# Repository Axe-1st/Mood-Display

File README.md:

# Mood-Display
## A Round Pin badge display! Powered by an Integrated ESP32-S3-WROOM-1 and a 1.28 in round display MoodBadge clips easily to your ID lanyard, keychain, belt, Bag, and so many more. You can easily express your mood or any animations you want to play on the display!

> Hiya! This project is still in its designing stage! When i build it, I will make a step by step video how to assemble 

> PDF is available in Zine folder!

### I made this project because i was inspired by those mini circular displays that you can bring anywhere! 
### This exsist since i wanted a badge that i can interact with.
### This project is pretty easy to do, All you need to do is follow the tutorial (Scoll down)

### Some kind of important notes!
- This is powered by USB C <b>ONLY</b>
- yes that means you have to always have a powerbank around with u to power it!
- reason for this: It would increase project cost and its complexity. 

## Schematic

> for a much better image check the pdf in extras!

## PCB

## PCB Render
- back

- Front

## Cad
- Onshape link:https://cad.onshape.com/documents/fe18899c0fc823d496ae247b/w/1ef647bd25a6a14e89f050fb/e/3a17c80e85047fb88fb13b3e?renderMode=0&uiState=6a0dad73ebc90dae0eac1fbd

> I love Onshape Man

## How to Build it 
- 1st step: Get the Requied materials in BOM.CSV and get the Gerber file in the folder production.
- 2nd Step: Pay JLC PCB to Fabricate the PCB and Use the links in the BOM.CSV to order parts
> You should def order a stencil! But for this tutorial i will be doing it manualy

- 3rd Step: Get your solder paste then manualy little solder to each pad that needs a connection. Also have a tissue nearby!
> Remember Patience is better than Crashing Out!

- 4th step: Start placing the compoments then when you are ready, use a hot plate to reflow all of the connections!
> For this part you would be Placing compoments at the back of the pcb so that means the front side of the pcb is facing flat on the hotplate
> When reflowing feel free to gently adjust the possiton of the compoments!

- 5th step: Now you have the backside of the pcb done! After letting the PCB rest now flip it to the other side, you should see some pads there. You are going to use a normal soldering iron to solder the buttons and other DIP compoments like the power Headers!

- 6th Step: Congradulations! You are done with the PCB!! Now kindly please test it by powering it on with a type C cable (please make sure it gets enough power to boot). Flash the test firmware i have provided it should light up the leds!

- if you like the bare PCB you can now stop here and use any of the mounting holes to attach the Mood-Display with anything!

- After this it would be Optional to do the case!

- 7th Step: Print all of the Case Parts then start assembling it by starting with the bottom. With the Bottom place the pcb on top and it line up with the mounting holes! When it is fully alligned screw the holes! Now get your assembles Bottom Case and carefully insert it up to the "middle case part" then super glue it! Now place and glue the Top Cover!
> i have used the terms "bottom case" "Middle Part" "Top Cover" why? because i have provided three parts in the CAD. 

- Final Step: There is no final step Lmao. Enjoy your own Mood display!

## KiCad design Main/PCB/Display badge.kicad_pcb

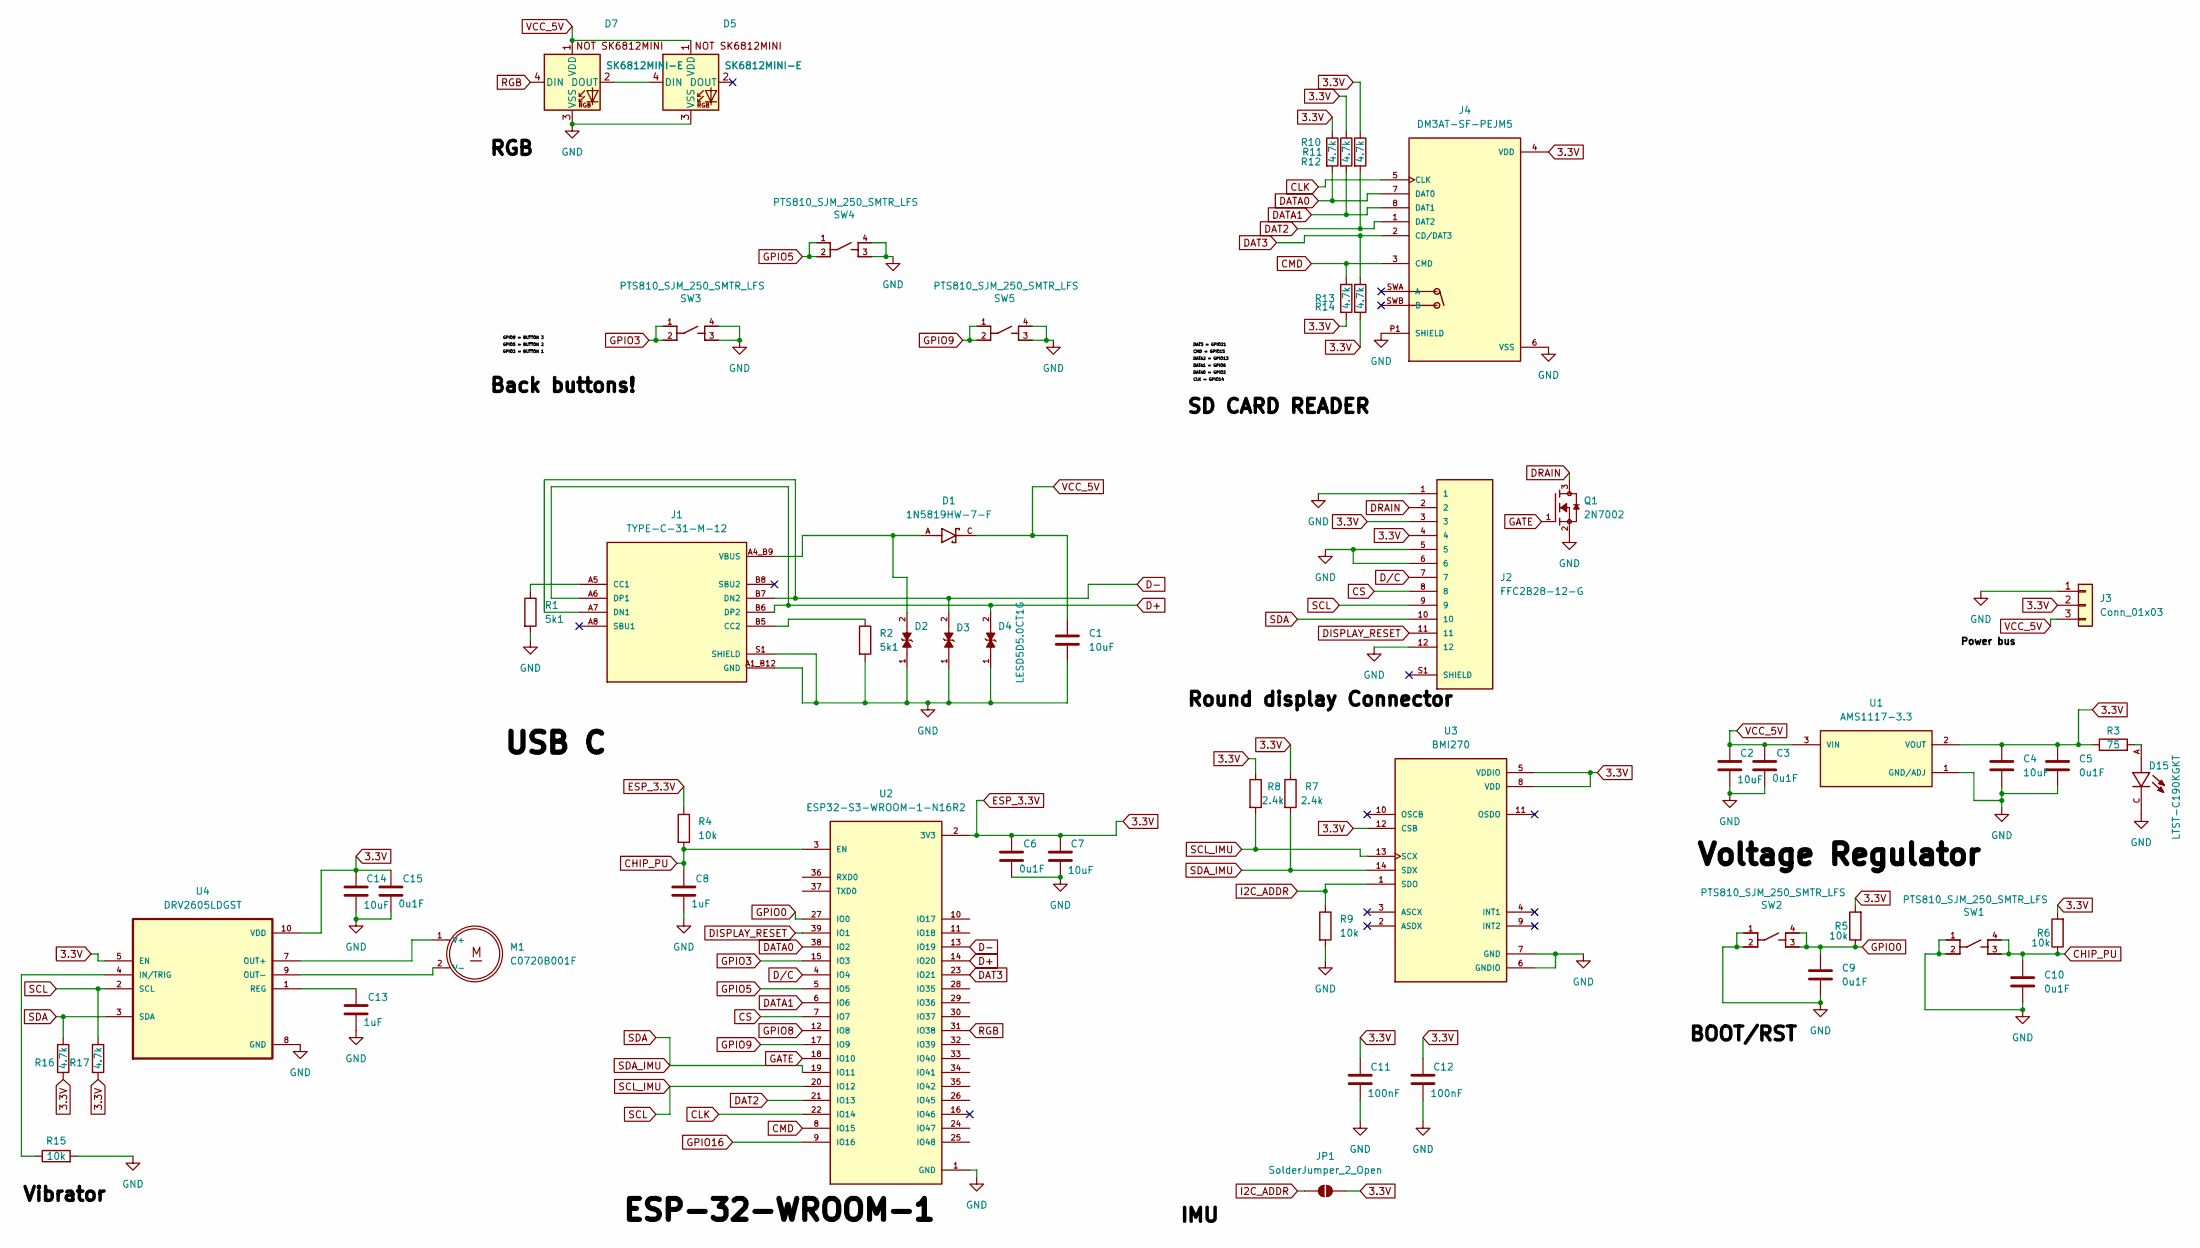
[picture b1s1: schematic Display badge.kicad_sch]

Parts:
C1, C2, C4, C7, C14: 10uF; C_0805_2012Metric_Pad1.18x1.45mm_HandSolder
C3, C5, C6, C9, C10, C15: 0u1F; C_0805_2012Metric_Pad1.18x1.45mm_HandSolder
C8, C13: 1uF; C_0805_2012Metric_Pad1.18x1.45mm_HandSolder
C11, C12: 100nF; C_0805_2012Metric_Pad1.18x1.45mm_HandSolder
D1: 1N5819HW-7-F; SOD3715X145N; PARTREV 18-2
D2, D3, D4: LESD5D5.0CT1G; TVS_LESD5D5.0CT1G; PARTREV O
D5, D7: SK6812MINI-E; SK6812MINI-E_fixed
D15: LTST-C190KGKT; LEDC1608X35N
J1: TYPE-C-31-M-12; HRO_TYPE-C-31-M-12; PARTREV 2020.12.08
J2: FFC2B28-12-G; GCT_FFC2B28-12-G; PARTREV A
J3: Conn_01x03; PinSocket_1x03_P2.00mm_Vertical
J4: DM3AT-SF-PEJM5; HRS_DM3AT-SF-PEJM5; PARTREV 20200913
JP1: SolderJumper_2_Open; SolderJumper-2_P1.3mm_Open_RoundedPad1.0x1.5mm
M1: C0720B001F; XDCR_C0720B001F
Q1: 2N7002; TRANS_2N7002; PARTREV 2023-01-11
R1, R2: 5k1; R_0805_2012Metric_Pad1.20x1.40mm_HandSolder
R3: 75; R_0805_2012Metric_Pad1.20x1.40mm_HandSolder
R4, R5, R6, R9, R15: 10k; R_0603_1608Metric_Pad0.98x0.95mm_HandSolder
R7, R8: 2.4k; RES_ERA2AEB242X
R10, R11, R12, R13, R14, R16, R17: 4.7k; R_0603_1608Metric_Pad0.98x0.95mm_HandSolder
SW1, SW2, SW3, SW4, SW5: PTS810_SJM_250_SMTR_LFS; SW_PTS810_SJM_250_SMTR_LFS
U1: AMS1117-3.3; SOT229P700X180-4N; PARTREV N/A
U2: ESP32-S3-WROOM-1-N16R2; XCVR_ESP32-S3-WROOM-1-N16R2; PARTREV v1.0
U3: BMI270; XDCR_BMI270
U4: DRV2605LDGST; SOP50P490X110-10N

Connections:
3.3V: C4.1, C5.1, C6.1, C7.1, C11.1, C12.1, C14.1, C15.1, J2.3, J2.4, J3.2, J4.4 (VDD), JP1.2 (B), R3.1, R4.1, R5.2, R6.2, R7.1, R8.1, R10.1, R11.1, R12.1, R13.2, R14.2, R16.2, R17.2, U1.2 (VOUT), U2.2 (3V3), U3.5 (VDDIO), U3.8 (VDD), U3.12 (CSB), U4.5 (EN), U4.10 (VDD)
CHIP_PU: C8.1, C10.1, R4.2, R6.1, SW1.3, SW1.4, U2.3 (EN)
CLK: J4.5 (CLK), U2.22 (IO14)
CMD: J4.3 (CMD), R13.1, U2.8 (IO15)
CS: J2.8, U2.7 (IO7)
D+: D4.2, J1.A6 (DP1), J1.B6 (DP2), U2.14 (IO20)
D-: D3.2, J1.A7 (DN1), J1.B7 (DN2), U2.13 (IO19)
DAT2: J4.1 (DAT2), R12.2, U2.21 (IO13)
DAT3: J4.2 (CD/DAT3), R14.1, U2.23 (IO21)
DATA0: J4.7 (DAT0), R10.2, U2.38 (IO2)
DATA1: J4.8 (DAT1), R11.2, U2.6 (IO6)
DISPLAY_RESET: J2.11, U2.39 (IO1)
DRAIN: J2.2, Q1.3
D/C: J2.7, U2.4 (IO4)
GATE: Q1.1, U2.18 (IO10)
GND: C1.2, C2.2, C3.2, C4.2, C5.2, C6.2, C7.2, C8.2, C9.2, C10.2, C11.2, C12.2, C13.2, C14.2, C15.2, D2.1, D3.1, D4.1, D5.3 (VSS), D7.3 (VSS), D15.C, J1.A1_B12 (GND), J1.B1_A12 (GND), J1.S1 (SHIELD), J1.S2 (SHIELD), J1.S3 (SHIELD), J1.S4 (SHIELD), J2.1, J2.5, J2.6, J2.12, J3.1, J4.6 (VSS), J4.P1 (SHIELD), J4.P2 (SHIELD), J4.P3 (SHIELD), J4.P4 (SHIELD), Q1.2, R1.2, R2.2, R9.2, R15.2, SW1.1, SW1.2, SW2.1, SW2.2, SW3.3, SW3.4, SW4.3, SW4.4, SW5.3, SW5.4, U1.1 (GND/ADJ), U2.1 (GND), U2.40 (GND), U2.41_1 (GND), U2.41_2 (GND), U2.41_3 (GND), U2.41_4 (GND), U2.41_5 (GND), U2.41_6 (GND), U2.41_7 (GND), U2.41_8 (GND), U2.41_9 (GND), U3.6 (GNDIO), U3.7 (GND), U4.8 (GND)
GPIO0: C9.1, R5.1, SW2.3, SW2.4, U2.27 (IO0)
GPIO3: SW3.1, SW3.2, U2.15 (IO3)
GPIO5: SW4.1, SW4.2, U2.5 (IO5)
GPIO8: U2.12 (IO8)
GPIO9: SW5.1, SW5.2, U2.17 (IO9)
GPIO16: U2.9 (IO16)
I2C_ADDR: JP1.1 (A), R9.1, U3.1 (SDO)
unnamed: D5.4 (DIN), D7.2 (DOUT)
unnamed: D15.A, R3.2
unnamed: J1.A5 (CC1), R1.1
unnamed: J1.B5 (CC2), R2.1
unnamed: M1.1 (V+), U4.7 (OUT+)
unnamed: M1.2 (V-), U4.9 (OUT-)
unnamed: R15.1, U4.4 (IN/TRIG)
unnamed: C13.1, U4.1 (REG)
RGB: D7.4 (DIN), U2.31 (IO38)
SCL: J2.9, R8.2, R17.1, U2.20 (IO12), U3.13 (SCX), U4.2 (SCL)
SDA: J2.10, R7.2, R16.1, U2.19 (IO11), U3.14 (SDX), U4.3 (SDA)
VBUS: D1.A, D2.2, J1.A4_B9 (VBUS), J1.B4_A9 (VBUS)
VCC_5V: C1.1, C2.1, C3.1, D1.C, D5.1 (VDD), D7.1 (VDD), J3.3, U1.3 (VIN)

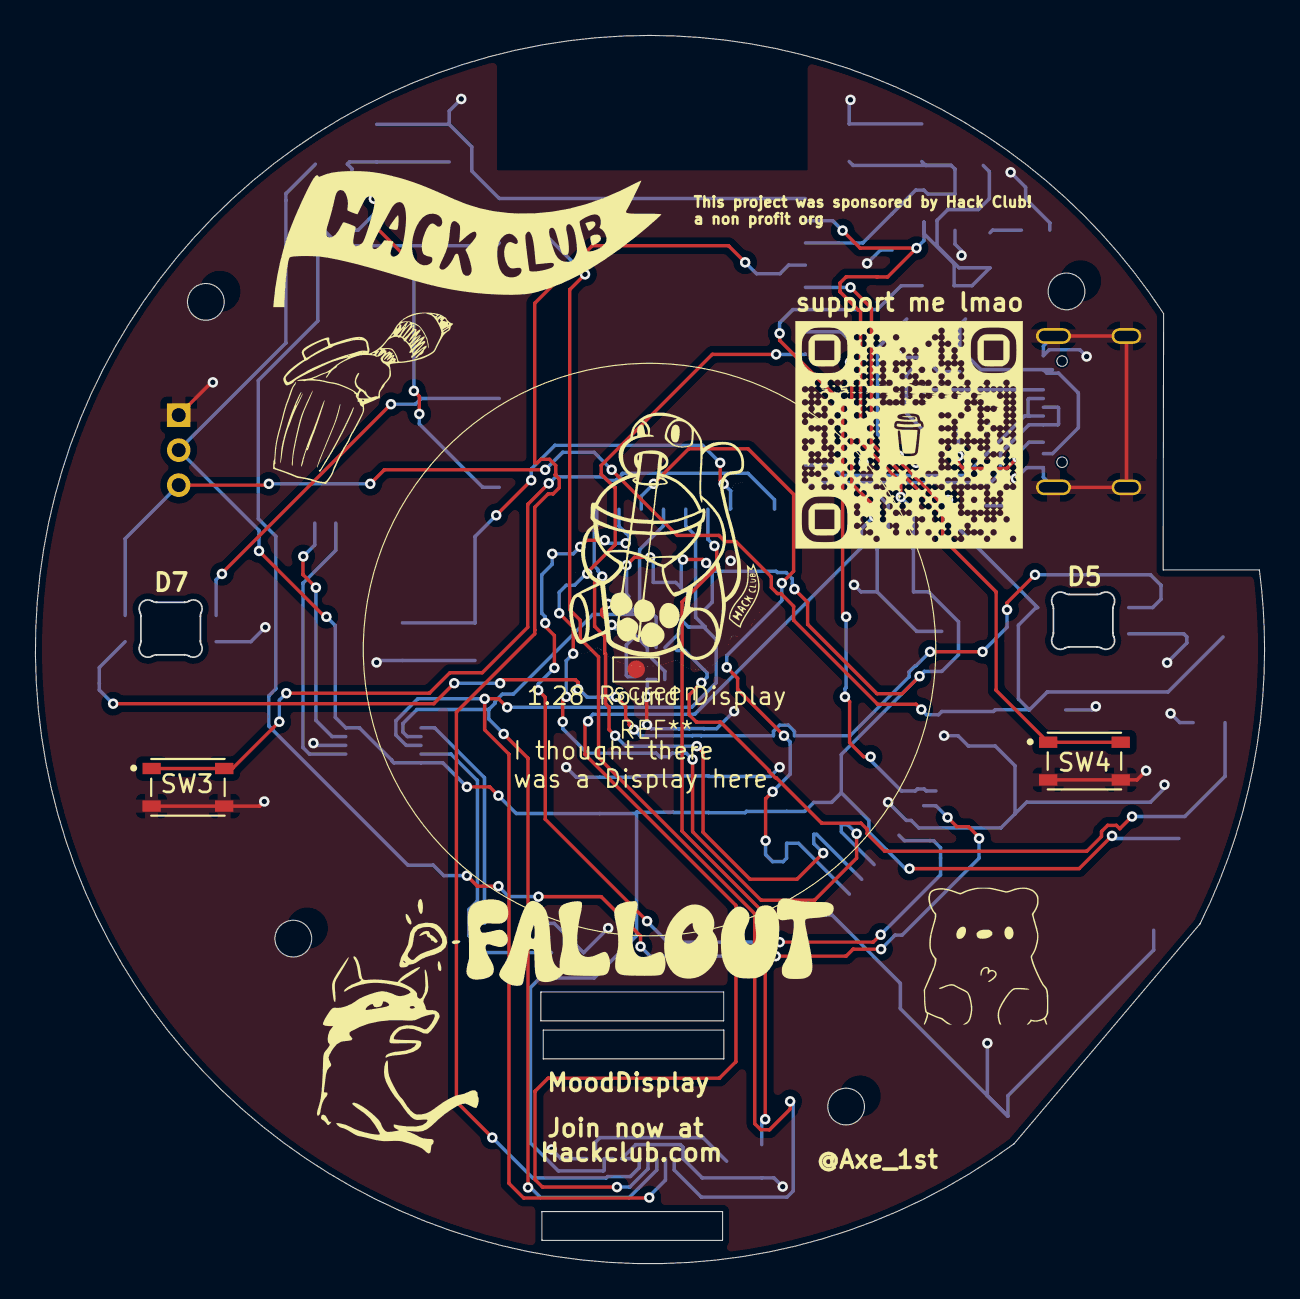
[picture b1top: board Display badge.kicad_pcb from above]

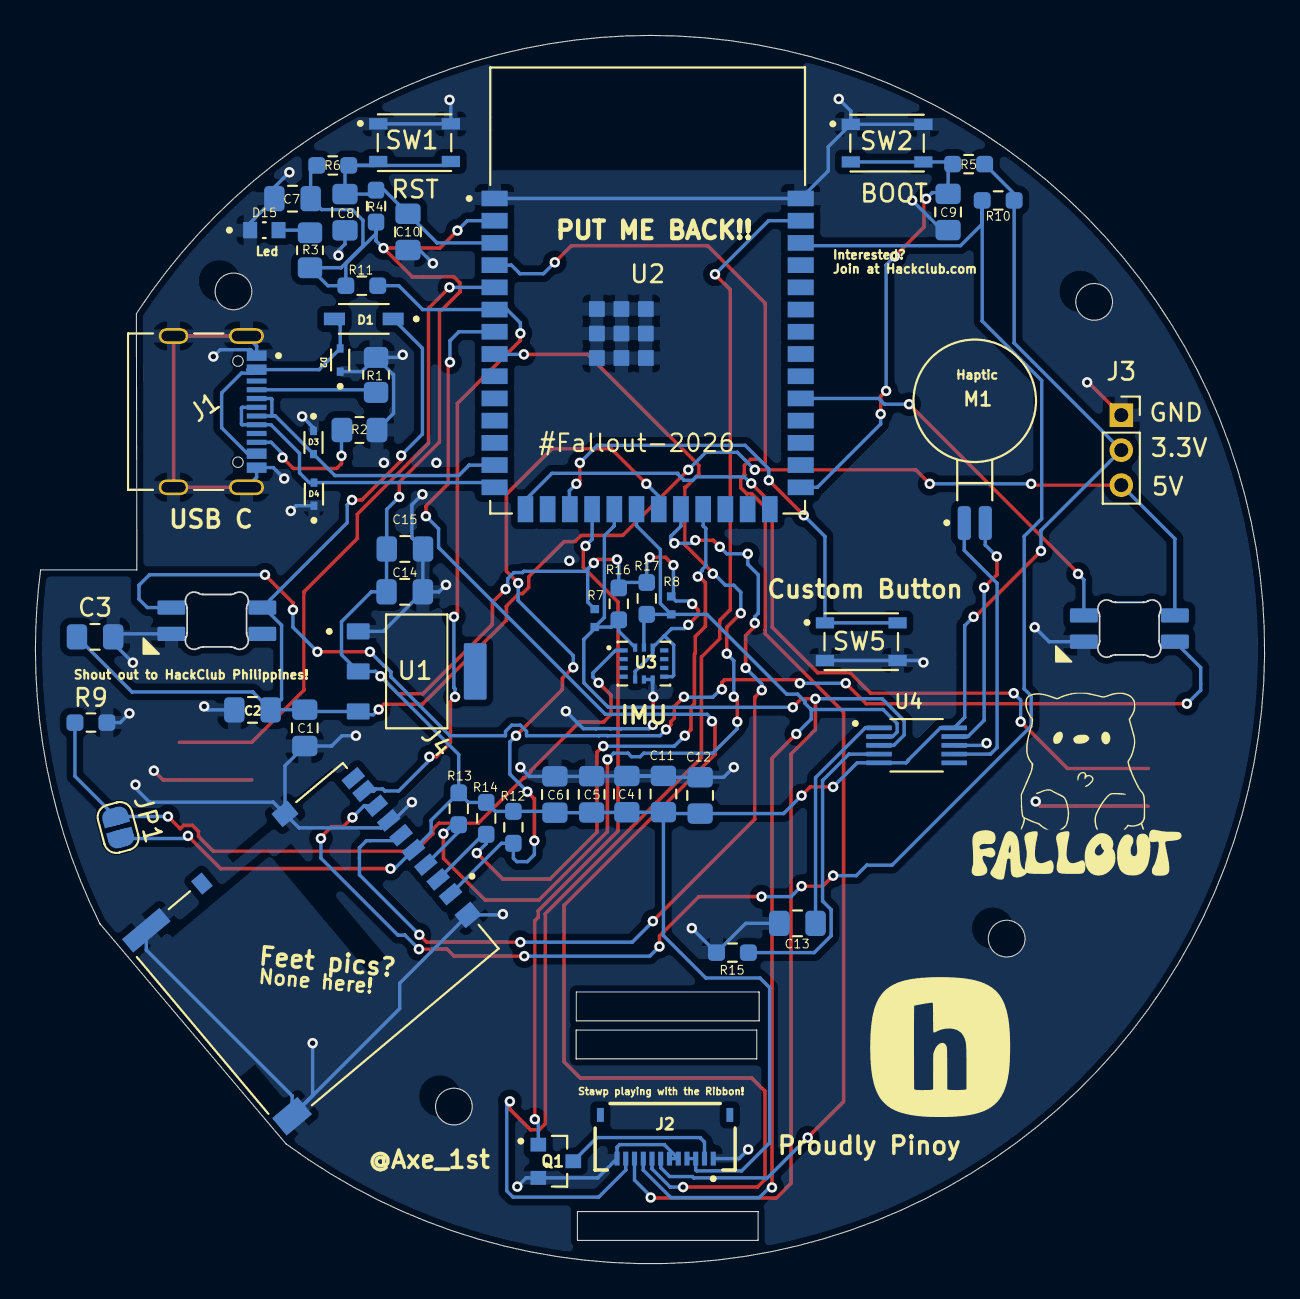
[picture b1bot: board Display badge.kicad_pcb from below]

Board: 2 copper layers, 70.3 x 70.2 mm, 55 parts (51 on the bottom side), 34 nets.

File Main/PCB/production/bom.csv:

Designator,Footprint,Quantity,Value,LCSC Part #
"C1, C14, C2, C4, C7",0805,5,10uF,
"C10, C15, C3, C5, C6, C9",0805,6,0u1F,
"C11, C12",0805,2,100nF,
"C13, C8",0805,2,1uF,
D1,SOD3715X145N,1,1N5819HW-7-F,
D15,LEDC1608X35N,1,LTST-C190KGKT,
"D2, D3, D4",TVS_LESD5D5.0CT1G,3,LESD5D5.0CT1G,
"D5, D7",SK6812MINI-E_fixed,2,SK6812MINI-E,
J1,HRO_TYPE-C-31-M-12,1,TYPE-C-31-M-12,
J2,GCT_FFC2B28-12-G,1,FFC2B28-12-G,
J3,PinSocket_1x03_P2.00mm_Vertical,1,Conn_01x03,
J4,HRS_DM3AT-SF-PEJM5,1,DM3AT-SF-PEJM5,
M1,XDCR_C0720B001F,1,C0720B001F,
Q1,TRANS_2N7002,1,2N7002,
"R1, R2",0805,2,5k1,
"R10, R11, R12, R13, R14, R16, R17",0603,7,4.7k,
"R15, R4, R5, R6, R9",0603,5,10k,
R3,0805,1,75,
"R7, R8",RES_ERA2AEB242X,2,2.4k,
"SW1, SW2, SW3, SW4, SW5",SW_PTS810_SJM_250_SMTR_LFS,5,PTS810_SJM_250_SMTR_LFS,
U1,SOT229P700X180-4N,1,AMS1117-3.3,
U2,XCVR_ESP32-S3-WROOM-1-N16R2,1,ESP32-S3-WROOM-1-N16R2,
U3,XDCR_BMI270,1,BMI270,
U4,SOP50P490X110-10N,1,DRV2605LDGST,

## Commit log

2026-05-20 Added Basic Repo requirements
2026-05-20 Update readme to V2
2026-05-20 Fixing new repo update
2026-05-20 update readme to V2 latest
2026-05-20 Update Repo
2026-05-20 Added the photos of readme
2026-05-20 Added CAD to Main
2026-05-27 ZINE IS OUT
2026-05-27 Fix image source and typos in README
    Updated image source and corrected typos in README.
2026-05-27 Update .gitignore to simplify badge backup paths
    Simplified the .gitignore entries for badge backups.
2026-05-27 Added BOM
2026-05-27 Enhance README with build steps and corrections
    Added detailed build instructions and fixed minor text issues.
2026-05-27 Zine Update
2026-05-28 Gitignore
2026-05-28 Rename Zine
2026-06-01 Update README with project status
    Added additional information about project status
2026-06-04 Fixed Buttons
    Fixed the buttons because the buttons are black which caused it to look like there is no buttons!
2026-06-05 Impov Case!
